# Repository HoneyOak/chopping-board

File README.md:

# Chopping Board

A minimal 40 key low-profile split ortholinear keyboard. Designed with simplicity and versatility in mind.

Split keyboards are a revelation in terms of ergonomics. I wanted to build a split ortholinear keyboard that looks clean and is designed with intention. I took aspects from the Corne and Totem to acheive this minimal yet complete keyboard.

## Features
- Hotswappable
- Low Profile
- 128x32 OLED on each side
- Low profile knobs on each side
- 40 keys
- _Flippable_ PCB _oO_
- Corne style thumb cluster
- Choc v1 switches
- ZMK Firmware
- Replicable, 3D printable and fully open source
# Images

## Schematic

## PCB

## Onshape
[Link to onshape document](https://cad.onshape.com/documents/f44f4f4ef5a39d6812b8dac0/w/095a0f8541f1a3b1fc930aaf/e/dd0d0b078a574b8c9309113b?renderMode=0&uiState=6880ba9a03652367c5f62c0e)

# Credits
- Erogogen - https://github.com/ergogen/ergogen
- Ceolide's Ergogen Footprints - https://github.com/ceoloide/ergogen-footprints

# BOM
#### Total Price: $105.18
| name                       | quantity | price US$     | total (US$) | link                                                                                                                                                                                                                                                                                                                                                                                                                                                                               | notes            |
| -------------------------- | -------- | ------------- | ----------- | ---------------------------------------------------------------------------------------------------------------------------------------------------------------------------------------------------------------------------------------------------------------------------------------------------------------------------------------------------------------------------------------------------------------------------------------------------------------------------------- | ---------------- |
| power switch               | 1        | 1.511627907   | 1.51        | [https://robu.in/product/pcm12smtr-ck-standing-paste-single-pole-double-throw-spdt-6v-smd-slide-switches-rohs/](https://robu.in/product/pcm12smtr-ck-standing-paste-single-pole-double-throw-spdt-6v-smd-slide-switches-rohs/)                                                                                                                                                                                                                                                     |                  |
| reset button               | 1        | 1.736046512   | 1.74        | [https://in.element14.com/c-k-components/pts636-sl43-smtr-lfs/tactile-switch-0-05a-12vdc-130gf/dp/3780603](https://in.element14.com/c-k-components/pts636-sl43-smtr-lfs/tactile-switch-0-05a-12vdc-130gf/dp/3780603)                                                                                                                                                                                                                                                               | 10 minimum order |
| ec12 rotary encoder        | 2        | 0.6976744186  | 1.40        | [https://rees52.com/products/rotary-encoder-ec12-audio-digital-potentiometer-5mm-handle-rs1258?variant=43607268524199&country=IN&currency=INR&utm_medium=product_sync&utm_source=google&utm_content=sag_organic&utm_campaign=sag_organic](https://rees52.com/products/rotary-encoder-ec12-audio-digital-potentiometer-5mm-handle-rs1258?variant=43607268524199&country=IN&currency=INR&utm_medium=product_sync&utm_source=google&utm_content=sag_organic&utm_campaign=sag_organic) |                  |
| m2 small screws            | 4        | 0.02744186047 | 0.11        | [https://onlyscrews.in/products/m2-x-6mm-phillips-pan-head-ss-304-screw?_pos=2&_sid=e9e4a7851&_ss=r](https://onlyscrews.in/products/m2-x-6mm-phillips-pan-head-ss-304-screw?_pos=2&_sid=e9e4a7851&_ss=r)                                                                                                                                                                                                                                                                           | Pack of 25       |
| m2 small heatset inserts   | 4        | 0.02197674419 | 0.09        | [https://onlyscrews.in/products/m2-x-3mm-brass-threaded-inserts](https://onlyscrews.in/products/m2-x-3mm-brass-threaded-inserts)                                                                                                                                                                                                                                                                                                                                                   |                  |
| supermini nrf52840         | 1        | 7.662790698   | 7.66        | [https://probots.co.in/pro-micro-nrf52840-development-board-compatible-with-nice-nano-v2-0.html](https://probots.co.in/pro-micro-nrf52840-development-board-compatible-with-nice-nano-v2-0.html)                                                                                                                                                                                                                                                                                   |                  |
| Kailh Choc Hotswap Sockets | 4        | 1.686046512   | 6.74        | [https://neomacro.in/products/kailh-choc-pg1350-hot-swap-sockets?variant=48049369907478&country=IN&currency=INR&utm_medium=product_sync&utm_source=google&utm_content=sag_organic&utm_campaign=sag_organic](https://neomacro.in/products/kailh-choc-pg1350-hot-swap-sockets?variant=48049369907478&country=IN&currency=INR&utm_medium=product_sync&utm_source=google&utm_content=sag_organic&utm_campaign=sag_organic)                                                             | Packs of 10      |
| Battery                    | 1        | 1.337209302   | 1.34        | [https://www.electropi.in/3.7v-90mah-lipo-battery-model-351028-india](https://www.electropi.in/3.7v-90mah-lipo-battery-model-351028-india)                                                                                                                                                                                                                                                                                                                                         |                  |
| SMD Diodes                 | 40       | 0.06488372093 | 2.60        | [https://evelta.com/1n4148w-7-f-switching-diode/](https://evelta.com/1n4148w-7-f-switching-diode/)                                                                                                                                                                                                                                                                                                                                                                                 |                  |
| Switches                   | 4        | 8.139534884   | 32.56       | [https://typeractive.xyz/products/choc-switches?variant=46024772387047](https://typeractive.xyz/products/choc-switches?variant=46024772387047)                                                                                                                                                                                                                                                                                                                                     | Packs of 10      |
| Keycaps 1                  | 4        | 4.651162791   | 18.60       | [https://typeractive.xyz/products/mbk-keycaps?variant=48512019497191](https://typeractive.xyz/products/mbk-keycaps?variant=48512019497191)                                                                                                                                                                                                                                                                                                                                         | Packs of 10      |
| Keycaps 1.5                | 1        | 2.325581395   | 2.33        | [https://typeractive.xyz/products/mbk-keycaps?variant=48512020283623](https://typeractive.xyz/products/mbk-keycaps?variant=48512020283623)                                                                                                                                                                                                                                                                                                                                         | Packs of 2       |
| Keycaps 1 homing           | 1        | 1.162790698   | 1.16        | [https://typeractive.xyz/products/mbk-keycaps?variant=48512019759335](https://typeractive.xyz/products/mbk-keycaps?variant=48512019759335)                                                                                                                                                                                                                                                                                                                                         | Packs of 2       |
| 128x32 OLED                | 2        | 1.476744186   | 2.953488372 | [https://www.electropi.in/0.91-inch-i2c-iic-128x32-oled-display-module?gPromoCode=EPJul2ndSale](https://www.electropi.in/0.91-inch-i2c-iic-128x32-oled-display-module?gPromoCode=EPJul2ndSale)                                                                                                                                                                                                                                                                                     |                  |
| PCB Fab                    | 1        | 24.39534884   | 24.40       | [https://www.lioncircuits.com](https://www.lioncircuits.com)                                                                                                                                                                                                                                                                                                                                                                                                                       | 5 minimum order  |
| Total                      |          |               | 105.18      |                                                                                                                                                                                                                                                                                                                                                                                                                                                                                    |                  |

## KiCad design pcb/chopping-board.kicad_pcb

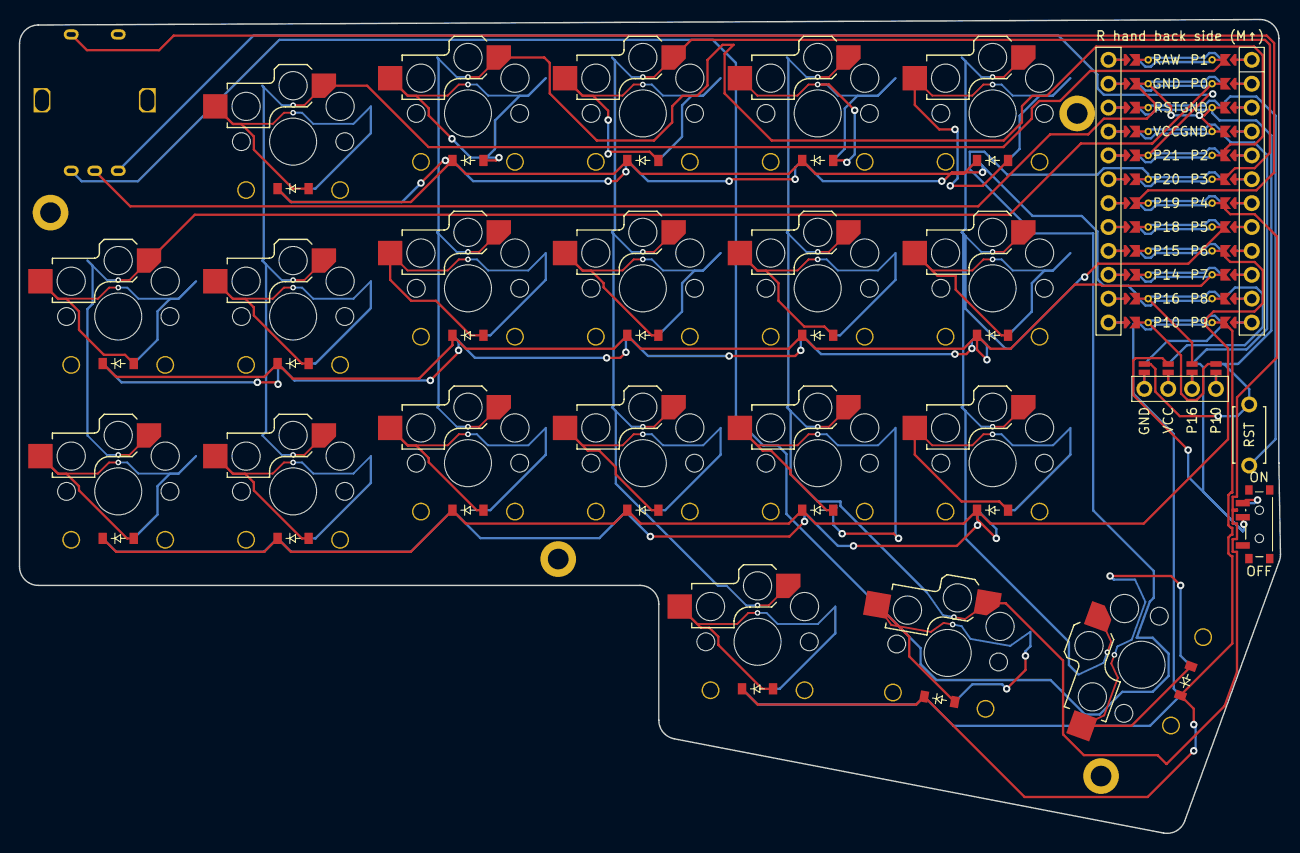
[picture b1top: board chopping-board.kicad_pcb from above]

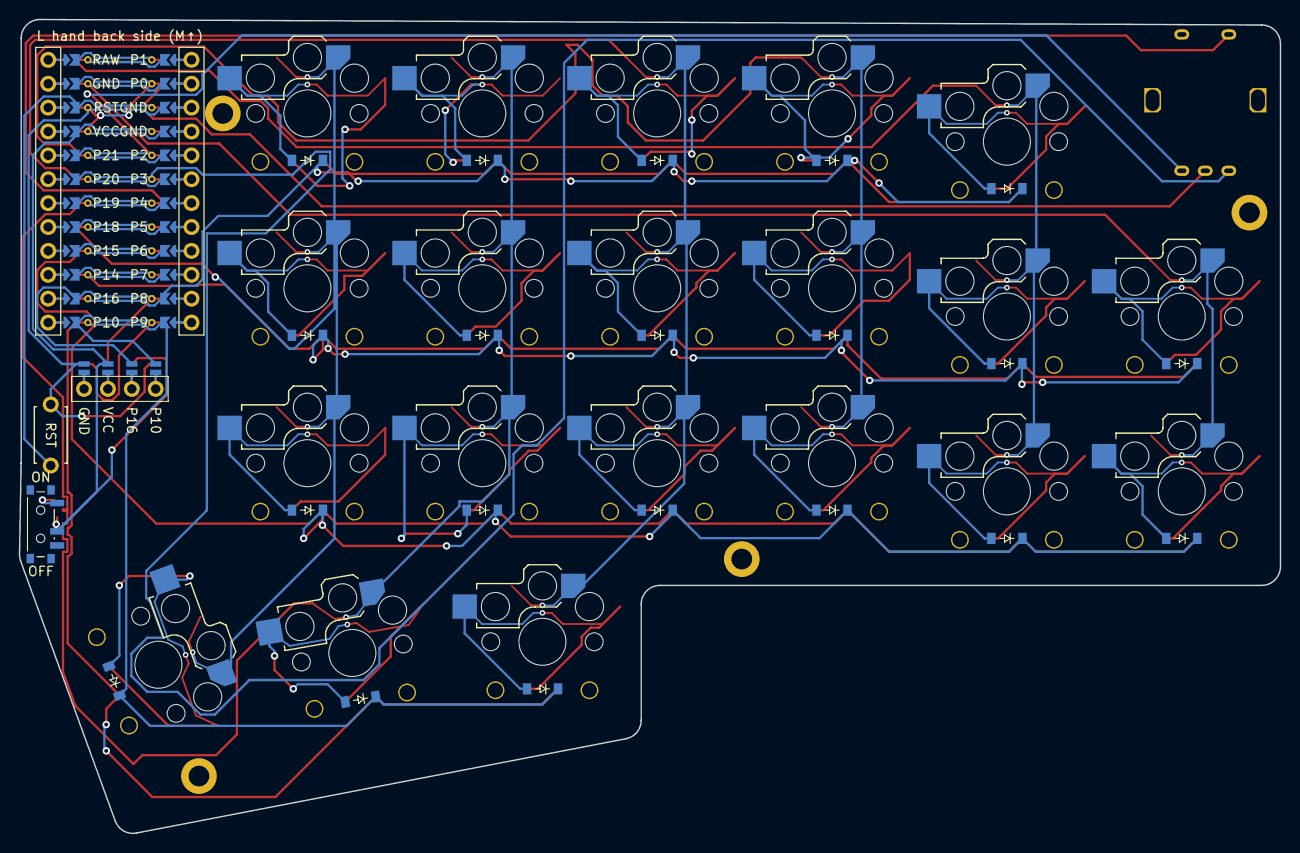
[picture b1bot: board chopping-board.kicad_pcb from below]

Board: 2 copper layers, 134.1 x 86.6 mm, 49 parts (20 on the bottom side), 43 nets.

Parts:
D1, D2, D3, D4, D5, D6, D7, D8, D9, D10, D11, D12, D13, D14, D15, D16, D17, D18, D19, D20: diode_tht_sod123
DISP1: display_ssd1306
H1, H2, H3, H4: mounting_hole_plated
MCU1: mcu_nice_nano
PWR1: power_switch_smd_side
RE1: rotary_encoder_ec11_ec12
RST1: reset_switch_tht_top
S1, S2, S3, S4, S5, S6, S7, S8, S9, S10, S11, S12, S13, S14, S15, S16, S17, S18, S19, S20: switch_choc_v1_v2

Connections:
BAT+: PWR1.1, PWR1.3
DISP1_1: DISP1.1, DISP1.10, DISP1.23
DISP1_2: DISP1.2, DISP1.11, DISP1.22
DISP1_3: DISP1.3, DISP1.12, DISP1.21
DISP1_4: DISP1.4, DISP1.13, DISP1.20
GND: DISP1.14, DISP1.24, MCU1.103, MCU1.104, MCU1.123, RE1.B, RST1.2
P0: MCU1.102, S1.1, S2.1
P1: MCU1.101, S3.1, S4.1, S5.1
P2: MCU1.105, S6.1, S7.1, S8.1
P3: MCU1.106, S9.1, S10.1, S11.1, S18.1
P4: MCU1.107, S12.1, S13.1, S14.1, S19.1
P5: MCU1.108, S15.1, S16.1, S17.1, S20.1
P6: D1.1, D3.1, D6.1, D9.1, D12.1, D15.1, MCU1.109
P7: D2.1, D4.1, D7.1, D10.1, D13.1, D16.1, MCU1.110
P8: D5.1, D8.1, D11.1, D14.1, D17.1, MCU1.111
P9: D18.1, D19.1, D20.1, MCU1.112
P10: DISP1.17, DISP1.27, MCU1.113
P16: DISP1.16, DISP1.26, MCU1.114
P19: MCU1.118, RE1.S1
P20: MCU1.119, RE1.C
P21: MCU1.120, RE1.A
RST: MCU1.122, RST1.1
VCC: DISP1.15, DISP1.25, MCU1.121, PWR1.2
index_bottom: D12.2, S12.2
index_home: D13.2, S13.2
index_top: D14.2, S14.2
inner_bottom: D15.2, S15.2
inner_extra: D18.2, S18.2
inner_home: D16.2, S16.2
inner_top: D17.2, S17.2
middle_bottom: D9.2, S9.2
middle_extra: D19.2, S19.2
middle_home: D10.2, S10.2
middle_top: D11.2, S11.2
outer_bottom: D1.2, S1.2
outer_extra: D20.2, S20.2
outer_home: D2.2, S2.2
pinky_bottom: D3.2, S3.2
pinky_home: D4.2, S4.2
pinky_top: D5.2, S5.2
ring_bottom: D6.2, S6.2
ring_home: D7.2, S7.2
ring_top: D8.2, S8.2

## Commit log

2025-07-25 Update BOM
2025-07-26 fix: move fw to prod
2025-07-30 add blend
2025-07-30 add blender assets
